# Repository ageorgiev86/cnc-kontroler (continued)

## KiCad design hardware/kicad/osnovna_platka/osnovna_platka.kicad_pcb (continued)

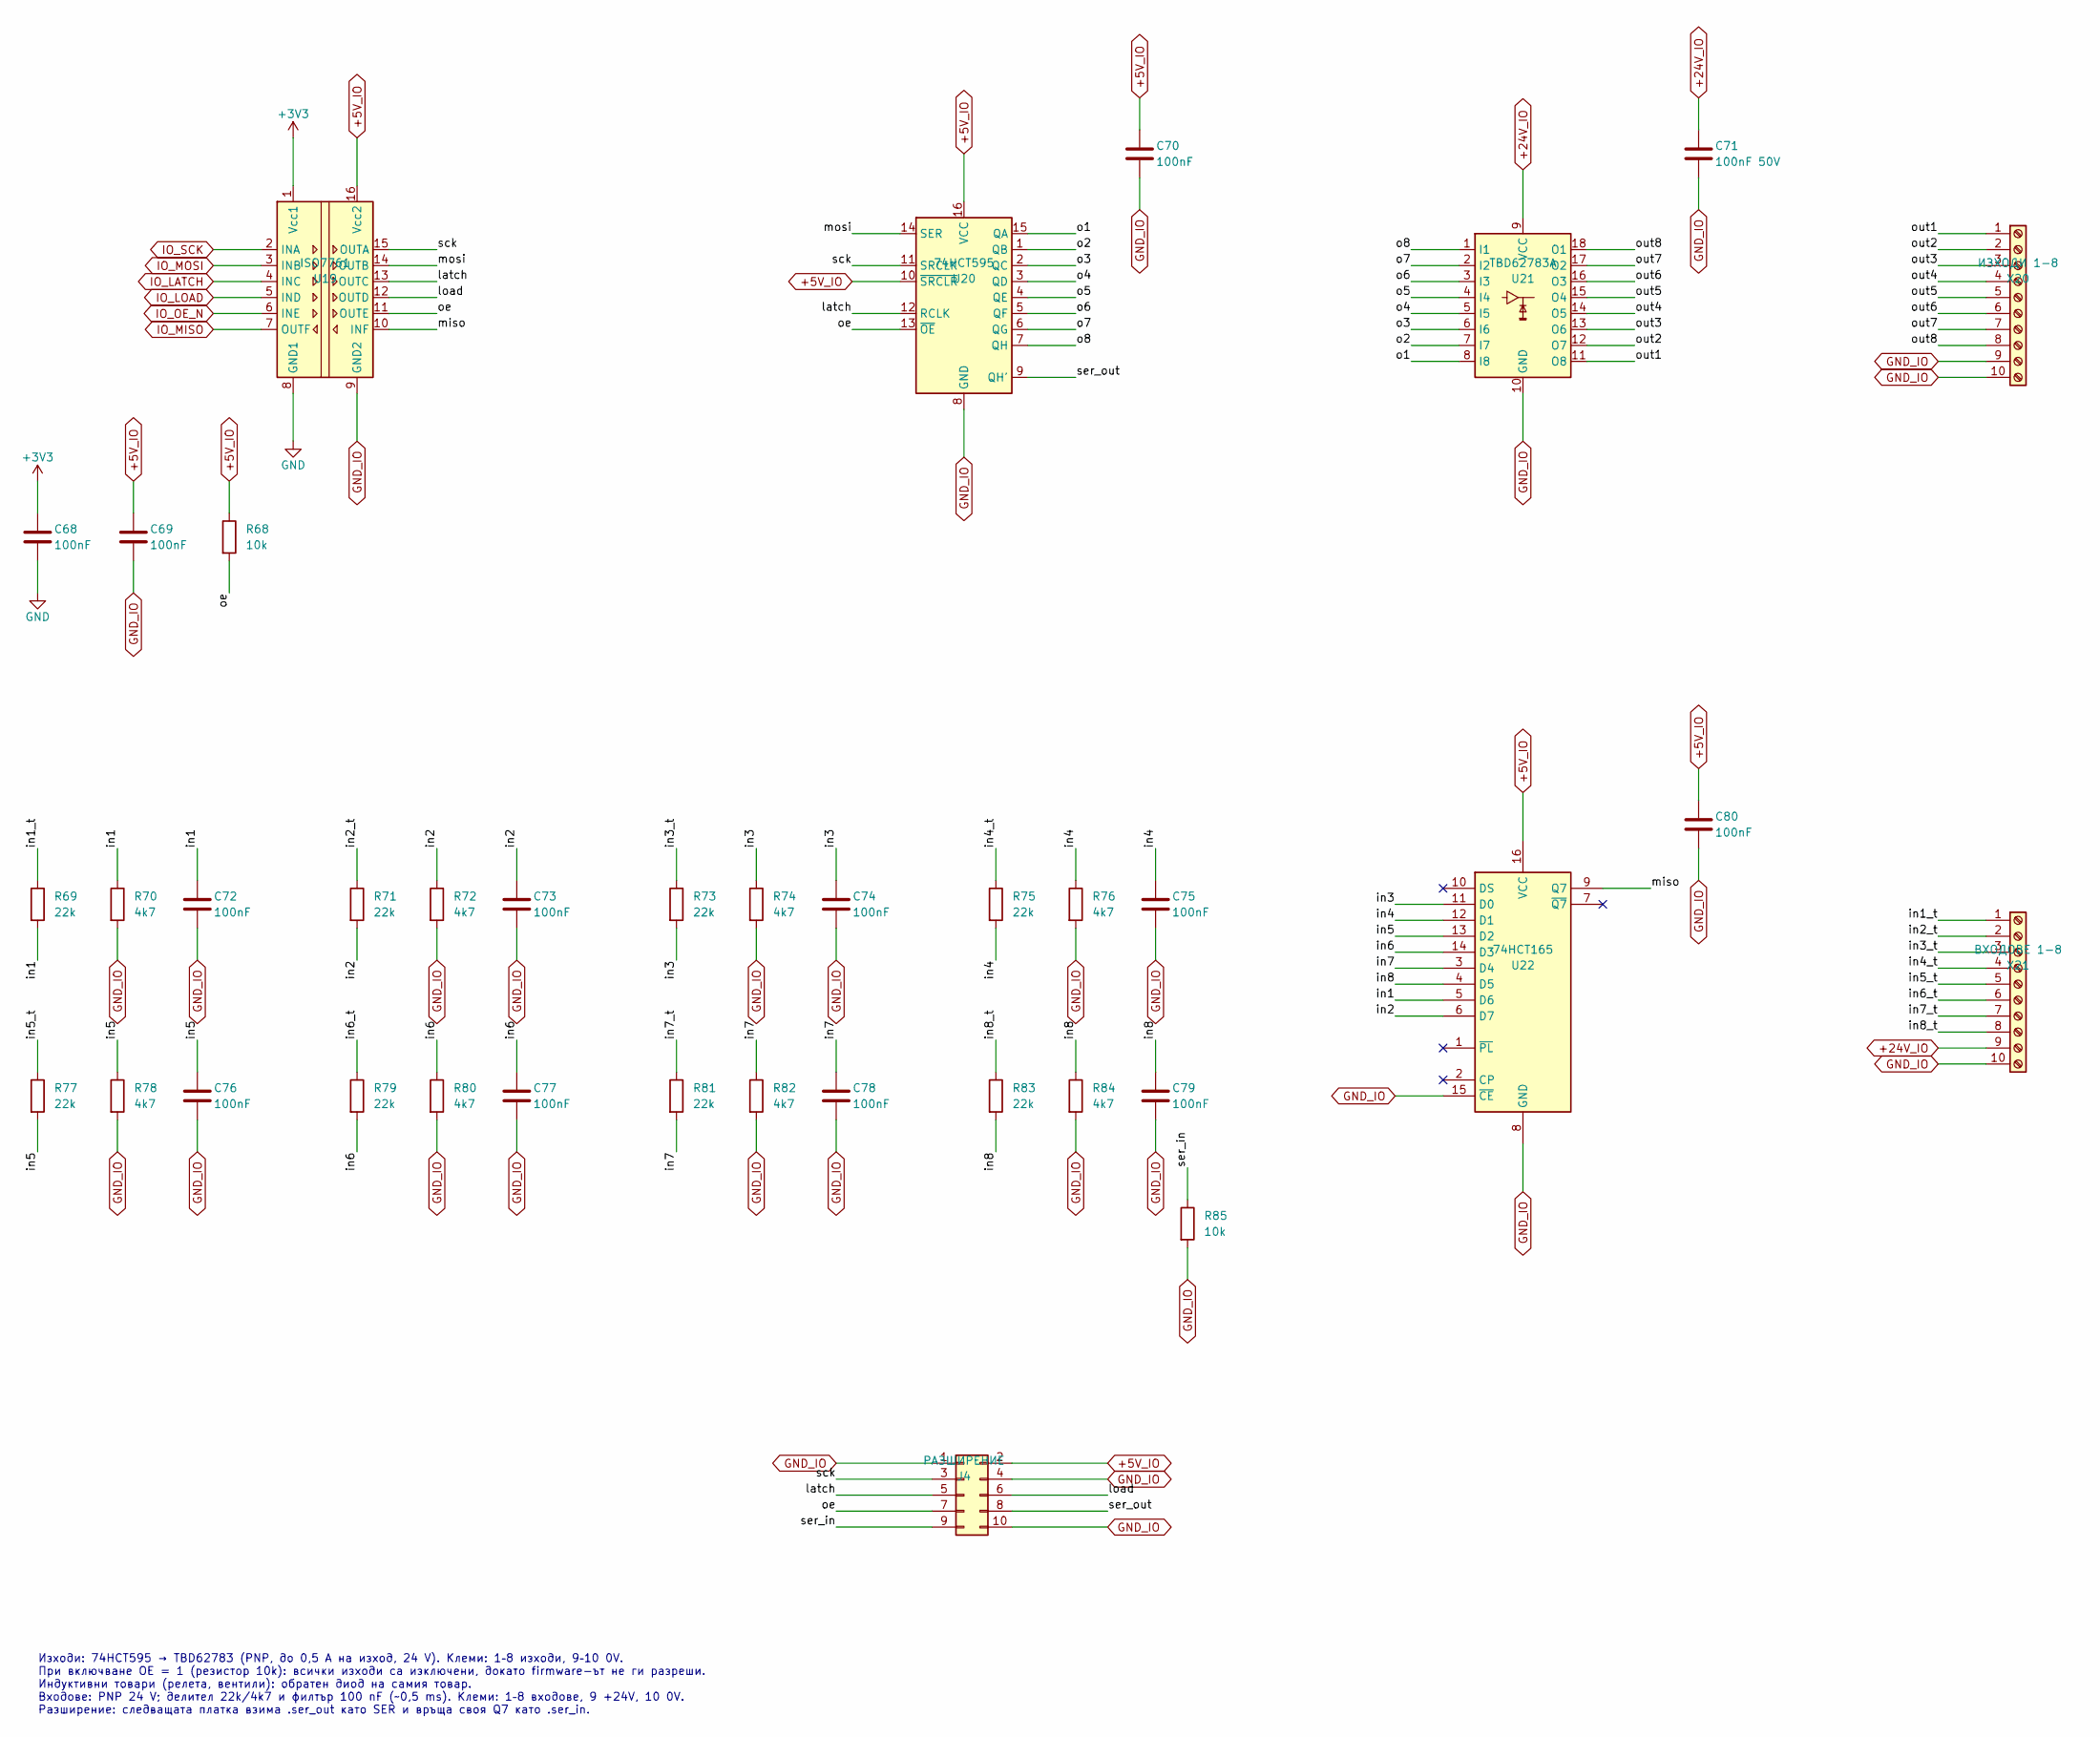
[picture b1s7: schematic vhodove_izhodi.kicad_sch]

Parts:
C68, C69, C70, C72, C73, C74, C75, C76, C77, C78, C79, C80: 100nF; C_0805_2012Metric
C71: 100nF 50V; C_0805_2012Metric
J4: РАЗШИРЕНИЕ; IDC-Header_2x05_P2.54mm_Vertical
R68, R85: 10k; R_0805_2012Metric
R69, R71, R73, R75, R77, R79, R81, R83: 22k; R_1206_3216Metric
R70, R72, R74, R76, R78, R80, R82, R84: 4k7; R_0805_2012Metric
U19: ISO7761; SOIC-16W_7.5x10.3mm_P1.27mm
U20: 74HCT595; SOIC-16_3.9x9.9mm_P1.27mm
U21: TBD62783A; SOIC-18W_7.5x11.6mm_P1.27mm
U22: 74HCT165; SOIC-16_3.9x9.9mm_P1.27mm
X20: ИЗХОДИ 1-8; PhoenixContact_MSTBA_2,5_10-G-5,08_1x10_P5.08mm_Horizontal
X21: ВХОДОВЕ 1-8; PhoenixContact_MSTBA_2,5_10-G-5,08_1x10_P5.08mm_Horizontal

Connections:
+3V3: C68.1, U19.1 (Vcc1); also elsewhere on the board
+5V_IO: C69.1, C70.1, C80.1, J4.2, R68.1, U19.16 (Vcc2), U20.10 (~SRCLR), U20.16 (VCC), U22.16 (VCC); also elsewhere on the board
+24V_IO: C71.1, U21.9 (VCC), X21.9; also elsewhere on the board
/Входове и изходи 8 + 8/in1: C72.1, R69.2, R70.1, U22.5 (D6)
/Входове и изходи 8 + 8/in1_t: R69.1, X21.1
/Входове и изходи 8 + 8/in2: C73.1, R71.2, R72.1, U22.6 (D7)
/Входове и изходи 8 + 8/in2_t: R71.1, X21.2
/Входове и изходи 8 + 8/in3: C74.1, R73.2, R74.1, U22.11 (D0)
/Входове и изходи 8 + 8/in3_t: R73.1, X21.3
/Входове и изходи 8 + 8/in4: C75.1, R75.2, R76.1, U22.12 (D1)
/Входове и изходи 8 + 8/in4_t: R75.1, X21.4
/Входове и изходи 8 + 8/in5: C76.1, R77.2, R78.1, U22.13 (D2)
/Входове и изходи 8 + 8/in5_t: R77.1, X21.5
/Входове и изходи 8 + 8/in6: C77.1, R79.2, R80.1, U22.14 (D3)
/Входове и изходи 8 + 8/in6_t: R79.1, X21.6
/Входове и изходи 8 + 8/in7: C78.1, R81.2, R82.1, U22.3 (D4)
/Входове и изходи 8 + 8/in7_t: R81.1, X21.7
/Входове и изходи 8 + 8/in8: C79.1, R83.2, R84.1, U22.4 (D5)
/Входове и изходи 8 + 8/in8_t: R83.1, X21.8
/Входове и изходи 8 + 8/latch: J4.5, U19.13 (OUTC), U20.12 (RCLK)
/Входове и изходи 8 + 8/load: J4.6, U19.12 (OUTD)
/Входове и изходи 8 + 8/miso: U19.10 (INF), U22.9 (Q7)
/Входове и изходи 8 + 8/mosi: U19.14 (OUTB), U20.14 (SER)
/Входове и изходи 8 + 8/o1: U20.15 (QA), U21.8 (I8)
/Входове и изходи 8 + 8/o2: U20.1 (QB), U21.7 (I7)
/Входове и изходи 8 + 8/o3: U20.2 (QC), U21.6 (I6)
/Входове и изходи 8 + 8/o4: U20.3 (QD), U21.5 (I5)
/Входове и изходи 8 + 8/o5: U20.4 (QE), U21.4 (I4)
/Входове и изходи 8 + 8/o6: U20.5 (QF), U21.3 (I3)
/Входове и изходи 8 + 8/o7: U20.6 (QG), U21.2 (I2)
/Входове и изходи 8 + 8/o8: U20.7 (QH), U21.1 (I1)
/Входове и изходи 8 + 8/oe: J4.7, R68.2, U19.11 (OUTE), U20.13 (~OE)
/Входове и изходи 8 + 8/out1: U21.11 (O8), X20.1
/Входове и изходи 8 + 8/out2: U21.12 (O7), X20.2
/Входове и изходи 8 + 8/out3: U21.13 (O6), X20.3
/Входове и изходи 8 + 8/out4: U21.14 (O5), X20.4
/Входове и изходи 8 + 8/out5: U21.15 (O4), X20.5
/Входове и изходи 8 + 8/out6: U21.16 (O3), X20.6
/Входове и изходи 8 + 8/out7: U21.17 (O2), X20.7
/Входове и изходи 8 + 8/out8: U21.18 (O1), X20.8
/Входове и изходи 8 + 8/sck: J4.3, U19.15 (OUTA), U20.11 (SRCLK)
/Входове и изходи 8 + 8/ser_in: J4.9, R85.1
/Входове и изходи 8 + 8/ser_out: J4.8, U20.9 (QH')
GND: C68.2, U19.8 (GND1); also elsewhere on the board
GND_IO: C69.2, C70.2, C71.2, C72.2, C73.2, C74.2, C75.2, C76.2, C77.2, C78.2, C79.2, C80.2, J4.1, J4.4, J4.10, R70.2, R72.2, R74.2, R76.2, R78.2, R80.2, R82.2, R84.2, R85.2, U19.9 (GND2), U20.8 (GND), U21.10 (GND), U22.8 (GND), U22.15 (~CE), X20.9, X20.10, X21.10; also elsewhere on the board
IO_LATCH: U19.4 (INC); also elsewhere on the board
IO_LOAD: U19.5 (IND); also elsewhere on the board
IO_MISO: U19.7 (OUTF); also elsewhere on the board
IO_MOSI: U19.3 (INB); also elsewhere on the board
IO_OE_N: U19.6 (INE); also elsewhere on the board
IO_SCK: U19.2 (INA); also elsewhere on the board

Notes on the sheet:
Изходи: 74HCT595 → TBD62783 (PNP, до 0,5 A на изход, 24 V). Клеми: 1–8 изходи, 9–10 0V. При включване OE = 1 (резистор 10k): всички изходи са изключени, докато firmware-ът не ги разреши. Индуктивни товари (релета, вентили): обратен диод на самия товар. Входове: PNP 24 V; делител 22k/4k7 и филтър 10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

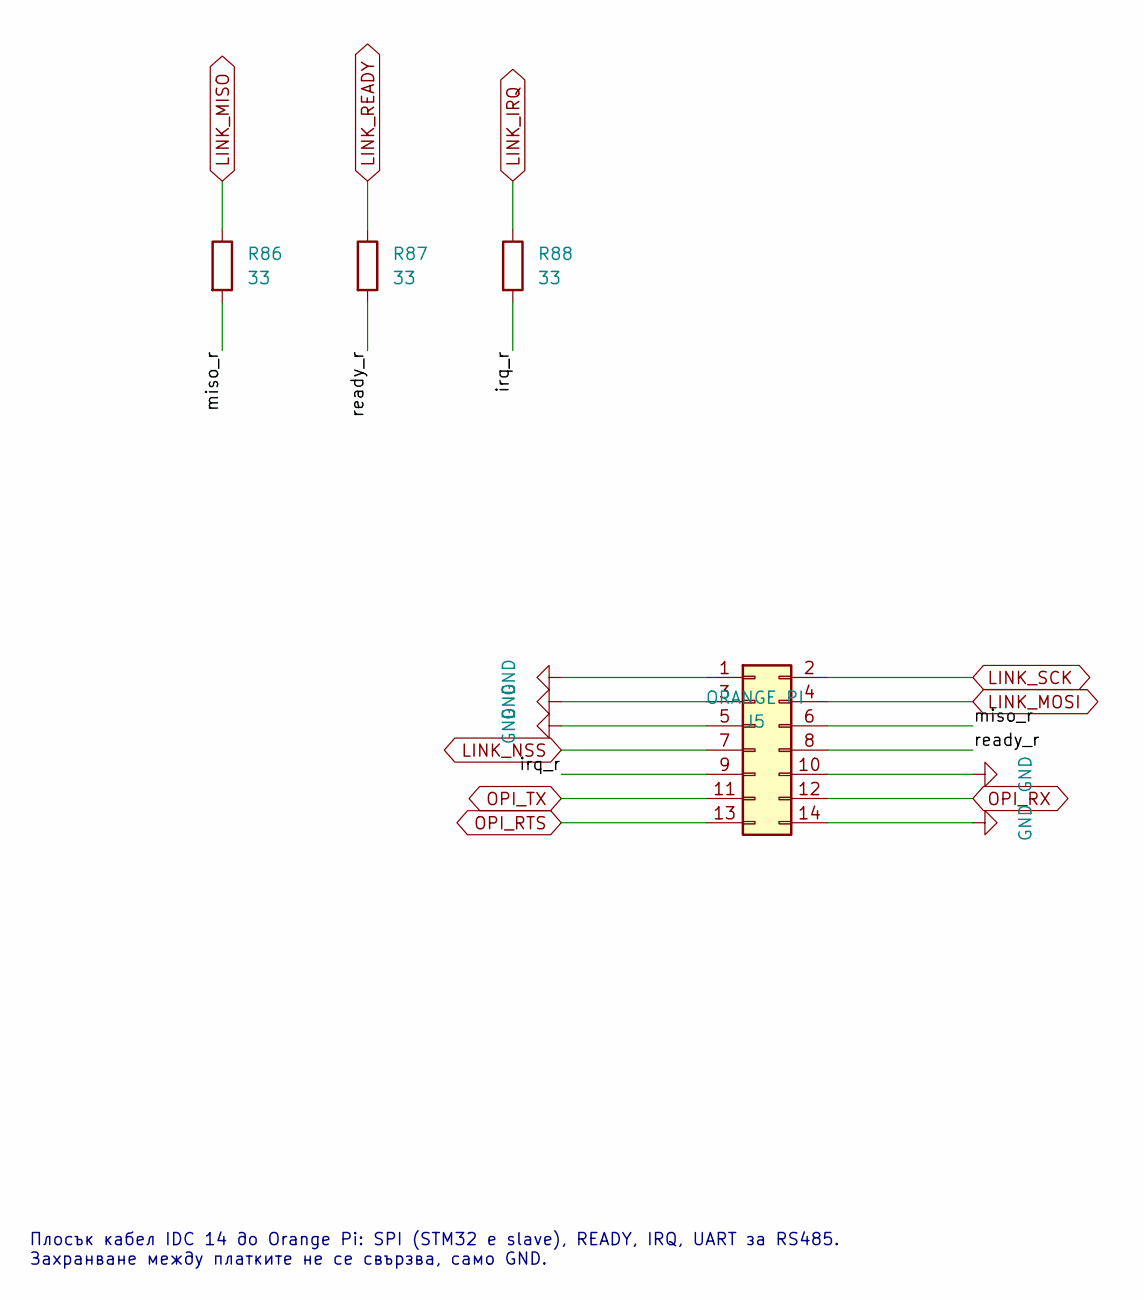
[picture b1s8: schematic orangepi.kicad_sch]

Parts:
J5: ORANGE PI; IDC-Header_2x07_P2.54mm_Vertical
R86, R87, R88: 33; R_0805_2012Metric

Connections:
/Orange Pi/irq_r: J5.9, R88.2
/Orange Pi/miso_r: J5.6, R86.2
/Orange Pi/ready_r: J5.8, R87.2
GND: J5.1, J5.3, J5.5, J5.10, J5.14; also elsewhere on the board
LINK_IRQ: R88.1; also elsewhere on the board
LINK_MISO: R86.1; also elsewhere on the board
LINK_MOSI: J5.4; also elsewhere on the board
LINK_NSS: J5.7; also elsewhere on the board
LINK_READY: R87.1; also elsewhere on the board
LINK_SCK: J5.2; also elsewhere on the board
OPI_RTS: J5.13; also elsewhere on the board
OPI_RX: J5.12; also elsewhere on the board
OPI_TX: J5.11; also elsewhere on the board

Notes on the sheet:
Плосък кабел IDC 14 до Orange Pi: SPI (STM32 е slave), READY, IRQ, UART за RS485. Захранване между платките не се свързва, само GND.

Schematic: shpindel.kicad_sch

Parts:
C81: 1uF; C_0805_2012Metric
C82: 100nF 50V; C_0805_2012Metric
C83: 100nF; C_0805_2012Metric
JP1: ТЕРМИНАТОР; PinHeader_1x02_P2.54mm_Vertical
R89, R91: 10k; R_0805_2012Metric
R90: 20k; R_0805_2012Metric
R92: 100; R_0805_2012Metric
R93, R94: 470; R_0805_2012Metric
R95, R96: 680; R_0805_2012Metric
R97: 120; R_0805_2012Metric
U23: LM358; SOIC-8_3.9x4.9mm_P1.27mm
U24, U25: PC817; SMDIP-4_W7.62mm
U26: THVD1450; SOIC-8_3.9x4.9mm_P1.27mm
X22: ЧЕСТОТЕН РЕГУЛАТОР; PhoenixContact_MSTBA_2,5_5-G-5,08_1x05_P5.08mm_Horizontal
X23: RS485; PhoenixContact_MSTBA_2,5_3-G-5,08_1x03_P5.08mm_Horizontal

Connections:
+3V3: C83.1, R95.1, U26.8 (VCC); also elsewhere on the board
+24V: C82.1, U23.8 (V+); also elsewhere on the board
/Шпиндел/aout: R90.1, R92.1, U23.1
/Шпиндел/avi: R92.2, X22.1
/Шпиндел/fb: R90.2, R91.1, U23.2 (-)
/Шпиндел/fwd: U24.4, X22.3
/Шпиндел/fwd_a: R93.2, U24.1
/Шпиндел/pwm_f: C81.1, R89.2, U23.3 (+)
/Шпиндел/rev: U25.4, X22.4
/Шпиндел/rev_a: R94.2, U25.1
/Шпиндел/rs_a: R95.2, R97.1, U26.6 (A), X23.1
/Шпиндел/rs_b: JP1.2, R96.1, U26.7 (B), X23.2
/Шпиндел/term: JP1.1, R97.2
/Шпиндел/u2o: U23.6 (-), U23.7
/Шпиндел/vfd_com: U24.3, U25.3, X22.5
GND: C81.2, C82.2, C83.2, R91.2, R96.2, U23.4 (V-), U23.5 (+), U24.2, U25.2, U26.5 (GND), X22.2, X23.3; also elsewhere on the board
OPI_RTS: U26.2 (~RE), U26.3 (DE); also elsewhere on the board
OPI_RX: U26.1 (RO); also elsewhere on the board
OPI_TX: U26.4 (DI); also elsewhere on the board
SPINDLE_DIR: R94.1; also elsewhere on the board
SPINDLE_EN: R93.1; also elsewhere on the board
SPINDLE_PWM: R89.1; also elsewhere on the board

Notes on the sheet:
Регулатор: 1 AVI (0–10 V) 2 ACM 3 FWD 4 REV 5 COM. 0–10 V не е изолиран. RS485 (Modbus от Orange Pi): джъмперът включва 120 Ω само на края на линията.

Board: 2 copper layers, 286 parts (0 on the bottom side), 249 nets, no tracks yet.

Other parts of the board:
H1, H2, H3, H4: M3; MountingHole_3.2mm_M3

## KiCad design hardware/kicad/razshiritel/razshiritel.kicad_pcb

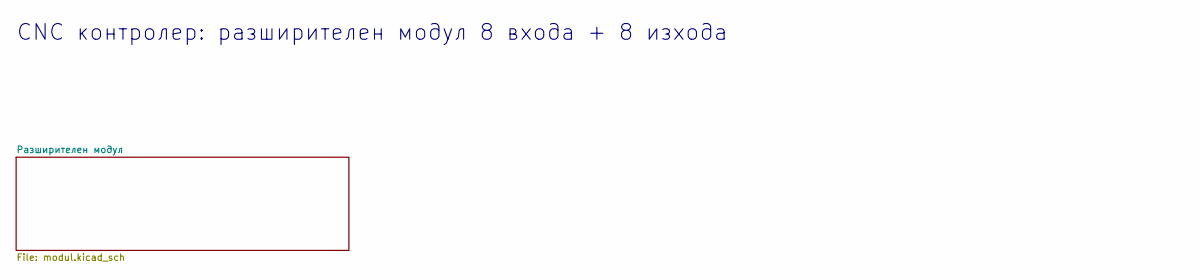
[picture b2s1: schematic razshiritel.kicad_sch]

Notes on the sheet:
CNC контролер: разширителен модул 8 входа + 8 изхода

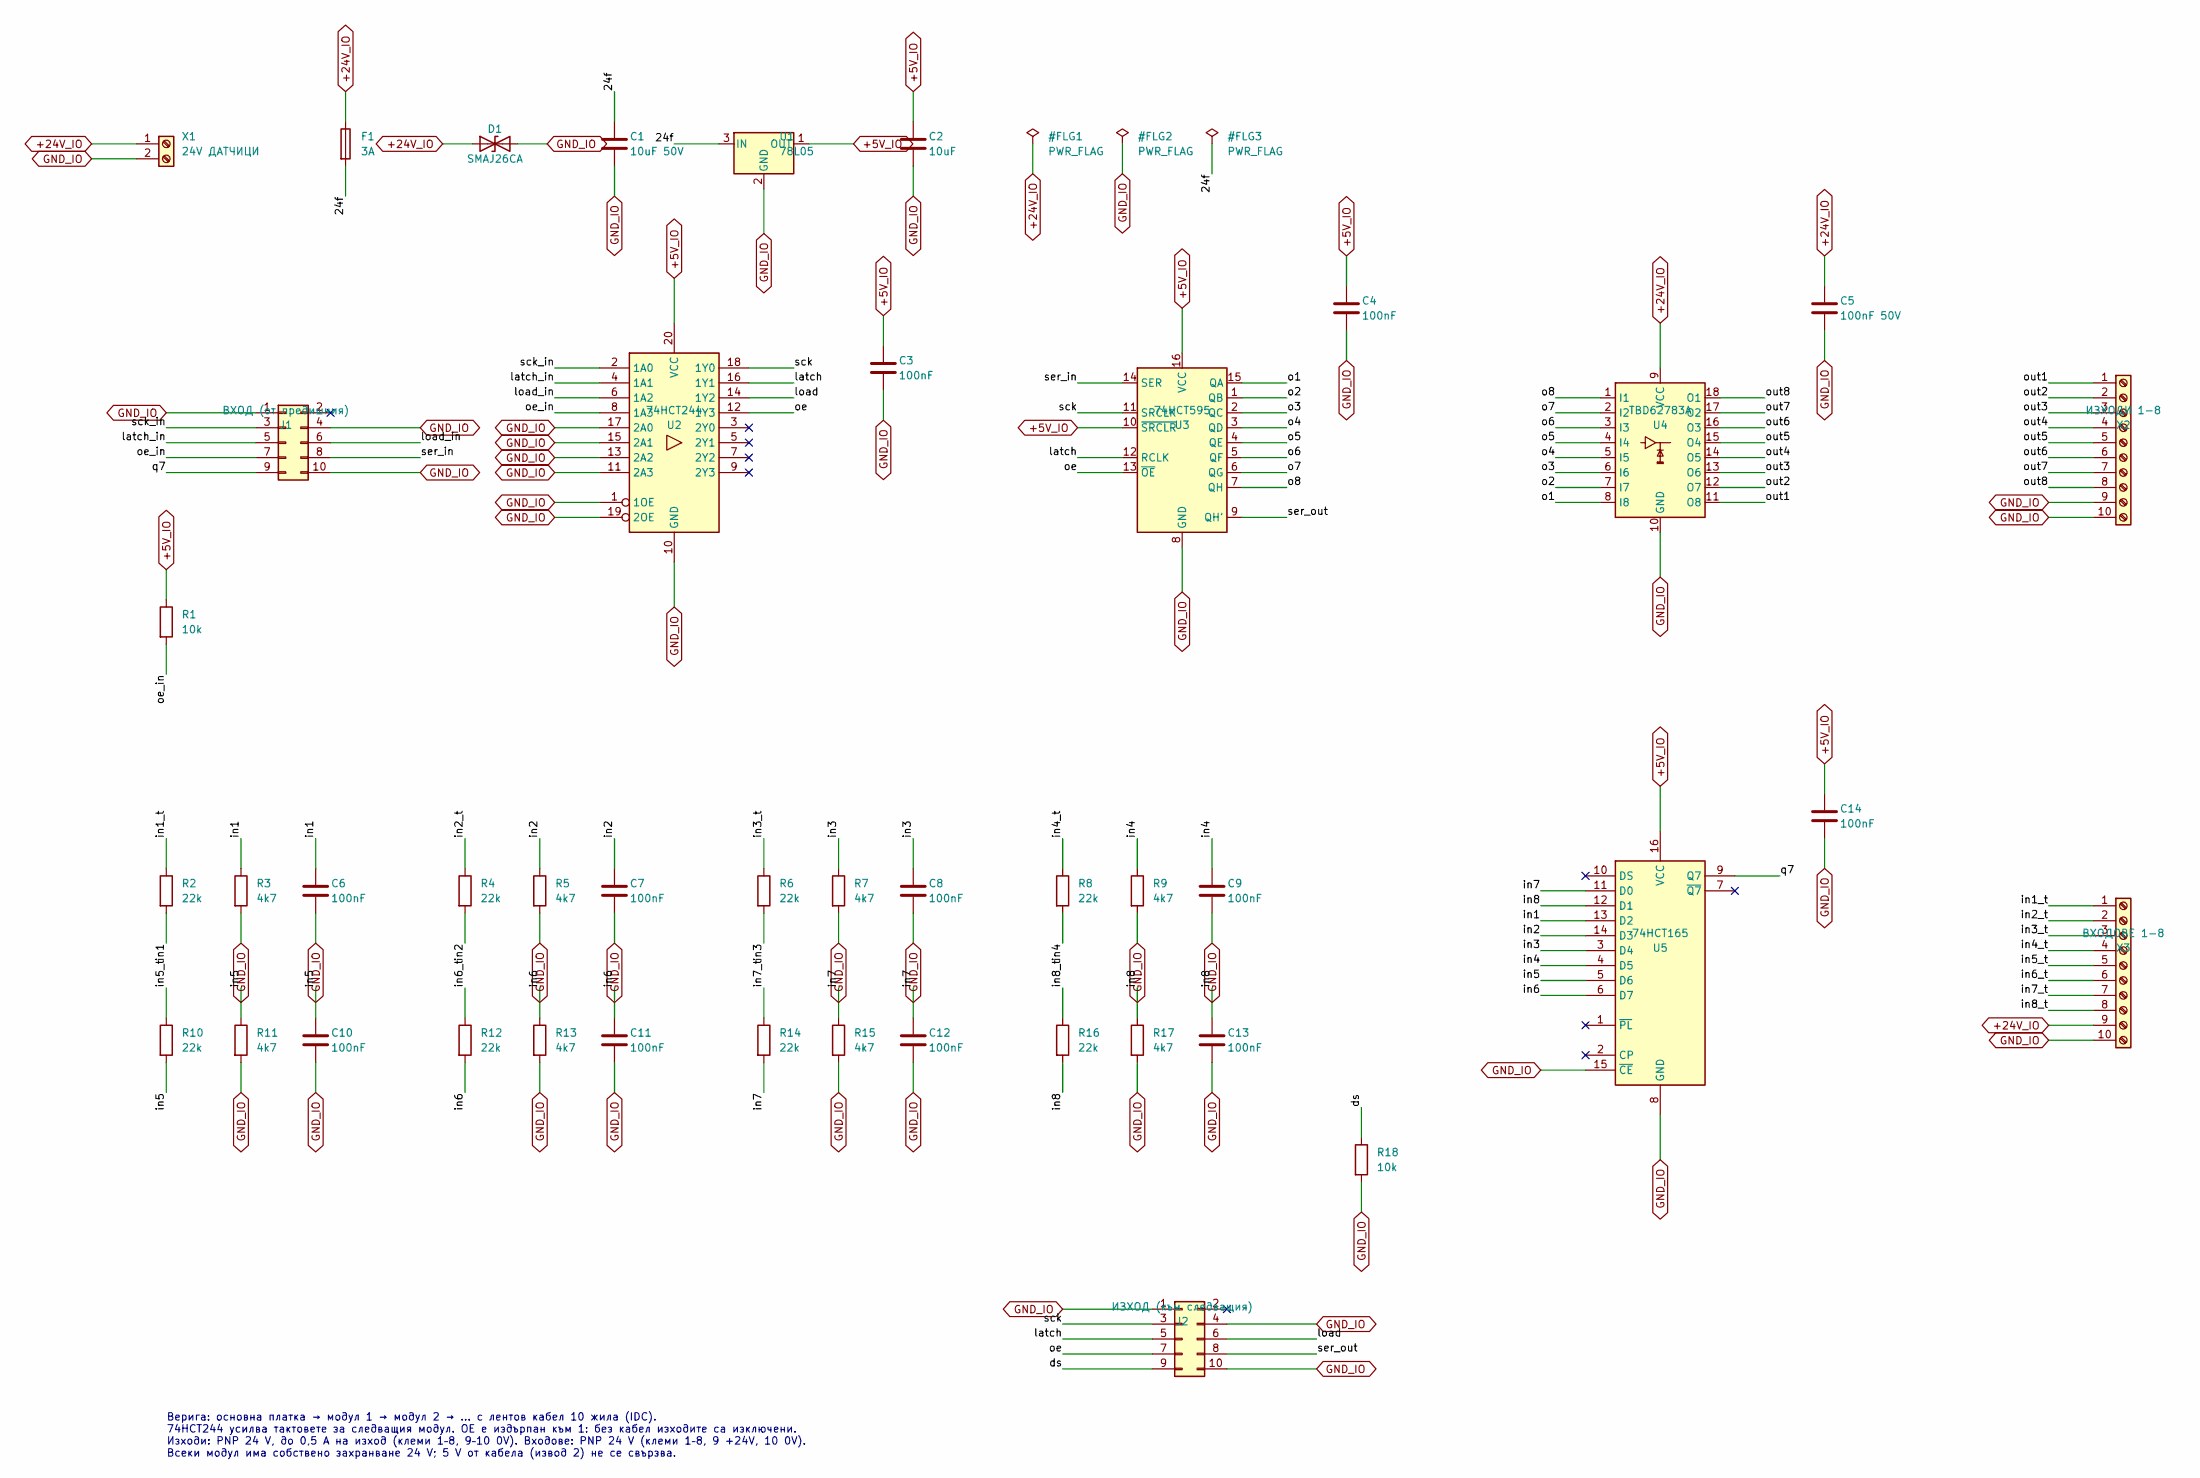
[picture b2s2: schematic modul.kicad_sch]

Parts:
C1: 10uF 50V; C_1210_3225Metric
C2: 10uF; C_1206_3216Metric
C3, C4, C6, C7, C8, C9, C10, C11, C12, C13, C14: 100nF; C_0805_2012Metric
C5: 100nF 50V; C_0805_2012Metric
D1: SMAJ26CA; D_SMA
F1: 3A; Fuse_1812_4532Metric
J1: ВХОД (от предишния); IDC-Header_2x05_P2.54mm_Vertical
J2: ИЗХОД (към следващия); IDC-Header_2x05_P2.54mm_Vertical
R1, R18: 10k; R_0805_2012Metric
R2, R4, R6, R8, R10, R12, R14, R16: 22k; R_1206_3216Metric
R3, R5, R7, R9, R11, R13, R15, R17: 4k7; R_0805_2012Metric
U1: 78L05; SOT-89-3
U2: 74HCT244; SOIC-20W_7.5x12.8mm_P1.27mm
U3: 74HCT595; SOIC-16_3.9x9.9mm_P1.27mm
U4: TBD62783A; SOIC-18W_7.5x11.6mm_P1.27mm
U5: 74HCT165; SOIC-16_3.9x9.9mm_P1.27mm
X1: 24V ДАТЧИЦИ; PhoenixContact_MSTBA_2,5_2-G-5,08_1x02_P5.08mm_Horizontal
X2: ИЗХОДИ 1-8; PhoenixContact_MSTBA_2,5_10-G-5,08_1x10_P5.08mm_Horizontal
X3: ВХОДОВЕ 1-8; PhoenixContact_MSTBA_2,5_10-G-5,08_1x10_P5.08mm_Horizontal

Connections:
+5V_IO: C2.1, C3.1, C4.1, C14.1, R1.1, U1.1 (OUT), U2.20 (VCC), U3.10 (~SRCLR), U3.16 (VCC), U5.16 (VCC)
+24V_IO: C5.1, D1.1 (A1), F1.1, U4.9 (VCC), X1.1, X3.9
/Разширителен модул/24f: C1.1, F1.2, U1.3 (IN)
/Разширителен модул/ds: J2.9, R18.1
/Разширителен модул/in1: C6.1, R2.2, R3.1, U5.13 (D2)
/Разширителен модул/in1_t: R2.1, X3.1
/Разширителен модул/in2: C7.1, R4.2, R5.1, U5.14 (D3)
/Разширителен модул/in2_t: R4.1, X3.2
/Разширителен модул/in3: C8.1, R6.2, R7.1, U5.3 (D4)
/Разширителен модул/in3_t: R6.1, X3.3
/Разширителен модул/in4: C9.1, R8.2, R9.1, U5.4 (D5)
/Разширителен модул/in4_t: R8.1, X3.4
/Разширителен модул/in5: C10.1, R10.2, R11.1, U5.5 (D6)
/Разширителен модул/in5_t: R10.1, X3.5
/Разширителен модул/in6: C11.1, R12.2, R13.1, U5.6 (D7)
/Разширителен модул/in6_t: R12.1, X3.6
/Разширителен модул/in7: C12.1, R14.2, R15.1, U5.11 (D0)
/Разширителен модул/in7_t: R14.1, X3.7
/Разширителен модул/in8: C13.1, R16.2, R17.1, U5.12 (D1)
/Разширителен модул/in8_t: R16.1, X3.8
/Разширителен модул/latch: J2.5, U2.16 (1Y1), U3.12 (RCLK)
/Разширителен модул/latch_in: J1.5, U2.4 (1A1)
/Разширителен модул/load: J2.6, U2.14 (1Y2)
/Разширителен модул/load_in: J1.6, U2.6 (1A2)
/Разширителен модул/o1: U3.15 (QA), U4.8 (I8)
/Разширителен модул/o2: U3.1 (QB), U4.7 (I7)
/Разширителен модул/o3: U3.2 (QC), U4.6 (I6)
/Разширителен модул/o4: U3.3 (QD), U4.5 (I5)
/Разширителен модул/o5: U3.4 (QE), U4.4 (I4)
/Разширителен модул/o6: U3.5 (QF), U4.3 (I3)
/Разширителен модул/o7: U3.6 (QG), U4.2 (I2)
/Разширителен модул/o8: U3.7 (QH), U4.1 (I1)
/Разширителен модул/oe: J2.7, U2.12 (1Y3), U3.13 (~OE)
/Разширителен модул/oe_in: J1.7, R1.2, U2.8 (1A3)
/Разширителен модул/out1: U4.11 (O8), X2.1
/Разширителен модул/out2: U4.12 (O7), X2.2
/Разширителен модул/out3: U4.13 (O6), X2.3
/Разширителен модул/out4: U4.14 (O5), X2.4
/Разширителен модул/out5: U4.15 (O4), X2.5
/Разширителен модул/out6: U4.16 (O3), X2.6
/Разширителен модул/out7: U4.17 (O2), X2.7
/Разширителен модул/out8: U4.18 (O1), X2.8
/Разширителен модул/q7: J1.9, U5.9 (Q7)
/Разширителен модул/sck: J2.3, U2.18 (1Y0), U3.11 (SRCLK)
/Разширителен модул/sck_in: J1.3, U2.2 (1A0)
/Разширителен модул/ser_in: J1.8, U3.14 (SER)
/Разширителен модул/ser_out: J2.8, U3.9 (QH')
GND_IO: C1.2, C2.2, C3.2, C4.2, C5.2, C6.2, C7.2, C8.2, C9.2, C10.2, C11.2, C12.2, C13.2, C14.2, D1.2 (A2), J1.1, J1.4, J1.10, J2.1, J2.4, J2.10, R3.2, R5.2, R7.2, R9.2, R11.2, R13.2, R15.2, R17.2, R18.2, U1.2 (GND), U2.1 (1OE), U2.10 (GND), U2.11 (2A3), U2.13 (2A2), U2.15 (2A1), U2.17 (2A0), U2.19 (2OE), U3.8 (GND), U4.10 (GND), U5.8 (GND), U5.15 (~CE), X1.2, X2.9, X2.10, X3.10

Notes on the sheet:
Верига: основна платка → модул 1 → модул 2 → ... с лентов кабел 10 жила (IDC). 74HCT244 усилва тактовете за следващия модул. OE е издърпан към 1: без кабел изходите са изключени. Изходи: PNP 24 V, до 0,5 A на изход (клеми 1–8, 9–10 0V). Входове: PNP 24 V (клеми 1–8, 9 +24V, 10 0V). Всеки модул има 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

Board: 2 copper layers, 48 parts (0 on the bottom side), 48 nets, no tracks yet.

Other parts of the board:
H1, H2, H3, H4: M3; MountingHole_3.2mm_M3

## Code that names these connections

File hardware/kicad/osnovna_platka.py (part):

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# ---------------------------------------------------------------------------
MCU = {
    # енкодери (таймер в encoder mode: A = CH1, B = CH2)
    'PA0': 'ENC1_A', 'PA1': 'ENC1_B',          # TIM5
    'PA15': 'ENC2_A', 'PB3': 'ENC2_B',         # TIM2
    'PF0': 'ENC3_A', 'PF1': 'ENC3_B',          # TIM23
    'PB4': 'ENC4_A', 'PB5': 'ENC4_B',          # TIM3
    'PB6': 'ENC5_A', 'PB7': 'ENC5_B',          # TIM4
    'PA8': 'ENC6_A', 'PA9': 'ENC6_B',          # TIM1
    'PF11': 'ENC_SP_A', 'PF12': 'ENC_SP_B',    # TIM24
    # MPG пулт: отделен модул по RS-485 (UART4, AF8), посоката от PD3
    'PD0': 'MPG_RX', 'PD1': 'MPG_TX', 'PD3': 'MPG_DE',
    # стъпки и посока, канал 1–6 (един порт: DMA → GPIOD BSRR)
    'PD4': 'STEP1', 'PD5': 'DIR1', 'PD6': 'STEP2', 'PD7': 'DIR2', 'PD8': 'STEP3', 'PD9': 'DIR3',
    'PD10': 'STEP4', 'PD11': 'DIR4', 'PD12': 'STEP5', 'PD13': 'DIR5', 'PD14': 'STEP6', 'PD15': 'DIR6',
    'PB11': 'DRV_EN', 'PE3': 'DRV_FAULT', 'PE9': 'DRV_OE_N',
    # крайни изключватели и HOME, канал 1–6 (активни при 0 след оптрона)
    'PG8': 'LIM1', 'PG9': 'LIM2', 'PG10': 'LIM3', 'PG11': 'LIM4', 'PG12': 'LIM5', 'PG13': 'LIM6',
    'PG14': 'HOME1', 'PG15': 'HOME2', 'PF6': 'HOME3', 'PF7': 'HOME4', 'PF8': 'HOME5', 'PF9': 'HOME6',
    # връзка с Orange Pi (SPI4 slave)
    'PE11': 'LINK_NSS', 'PE12': 'LINK_SCK', 'PE13': 'LINK_MISO', 'PE14': 'LINK_MOSI',
    'PE15': 'LINK_READY', 'PE10': 'LINK_IRQ',
    # входове и изходи (SPI2 master към 74HCT595 / 74HCT165 през изолатора)
    'PB13': 'IO_SCK', 'PB14': 'IO_MISO', 'PB15': 'IO_MOSI', 'PB12': 'IO_LATCH', 'PE7': 'IO_LOAD',
    'PE8': 'IO_OE_N',
    # бързи входове
    'PA7': 'PROBE', 'PB1': 'TOOLSETTER', 'PC13': 'ESTOP_SENSE',
    # шпиндел
    'PB9': 'SPINDLE_PWM', 'PC4': 'SPINDLE_DIR', 'PC5': 'SPINDLE_EN',
    # процесорна част
    'PA11': '.usb_dm', 'PA12': '.usb_dp', 'PA13': 'SWDIO', 'PA14': 'SWCLK',
    'PH0': '.hse_in', 'PH1': '.hse_out', 'PC14': '.lse_in', 'PC15': '.lse_out',
    'PG7': '.led',
    'NRST': 'NRST', 'BOOT0': '.boot0', 'PDR_ON': '+3V3', 'VBAT': '.vbat',
    'VDD': '+3V3', 'VDD33USB': '+3V3', 'VDDA': '.vdda', 'VREF+': '.vdda', 'VSS': 'GND', 'VSSA': 'GND',
    71: '.vcap1', 106: '.vcap2',     # VCAP: всеки със свой кондензатор (не се свързват заедно)
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    flag(sh, 271.78, 330.2, '.vdda')

    place(sh, 'Device:Crystal_GND24', 'Y', '25MHz', 360.68, 50.8,
          {1: '.hse_in', 3: '.hse_out', 2: 'GND', 4: 'GND'}, footprint='Crystal:Crystal_SMD_3225-4Pin_3.2x2.5mm',
          role='mcu.hse')
    C(sh, 381, 50.8, '22pF', '.hse_in', 'GND', 'mcu.chse1')
    C(sh, 393.7, 50.8, '22pF', '.hse_out', 'GND', 'mcu.chse2')
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    R(sh, x, y, '4k7', '.estop_in', '.estop_a', 'in.estop.r', FP_R1206)
    place(sh, 'Device:D', 'D', '1N4148W', x + 15.24, y + 10.16, {'A': 'GND_IO', 'K': '.estop_a'}, footprint=FP_SOD,
          role='in.estop.d')
    place(sh, 'Isolator:PC817', 'U', 'PC817', x + 40.64, y, {1: '.estop_a', 2: 'GND_IO', 3: 'GND', 4: 'ESTOP_SENSE'},
          footprint=FP_PC817, stub=7.62, role='in.estop.u')
    R(sh, x + 66.04, y, '10k', '+3V3', 'ESTOP_SENSE', 'in.estop.pu')
    C(sh, x + 78.74, y, '10nF', 'ESTOP_SENSE', 'GND', 'in.estop.c')
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# ---------------------------------------------------------------------------
def sheet_links(project):
    sh = Sheet('orangepi', 'Orange Pi', project)
    for i, (net, loc) in enumerate((('LINK_MISO', '.miso_r'), ('LINK_READY', '.ready_r'), ('LINK_IRQ', '.irq_r'))):
        R(sh, 45.72 + i * 15.24, 50.8, '33', net, loc, f'opi.r{i + 1}')
    place(sh, 'Connector_Generic:Conn_02x07_Odd_Even', 'J', 'ORANGE PI', 101.6, 101.6, {
        1: 'GND', 2: 'LINK_SCK', 3: 'GND', 4: 'LINK_MOSI', 5: 'GND', 6: '.miso_r', 7: 'LINK_NSS',
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# ---------------------------------------------------------------------------
def sheet_spindle(project):
    sh = Sheet('shpindel', 'Шпиндел', project)
    R(sh, 30.48, 50.8, '10k', 'SPINDLE_PWM', '.pwm_f', 'vfd.rf')
    C(sh, 45.72, 63.5, '1uF', '.pwm_f', 'GND', 'vfd.cf')
    ref = place(sh, 'Amplifier_Operational:LM358', 'U', 'LM358', 81.28, 55.88,
                {'+': '.pwm_f', '-': '.fb', 1: '.aout'}, footprint=FP_SOIC8, unit=1, role='vfd.op')
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    R(sh, 111.76, 50.8, '20k', '.aout', '.fb', 'vfd.rfb')
    R(sh, 111.76, 71.12, '10k', '.fb', 'GND', 'vfd.rg')
    R(sh, 129.54, 50.8, '100', '.aout', '.avi', 'vfd.rout')
    for i, (sig, out, nm) in enumerate((('SPINDLE_EN', '.fwd', 'fwd'), ('SPINDLE_DIR', '.rev', 'rev'))):
        x = 182.88 + i * 60.96
        R(sh, x, 50.8, '470', sig, f'{out}_a', f'vfd.{nm}.r')
        place(sh, 'Isolator:PC817', 'U', 'PC817', x + 27.94, 50.8,
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
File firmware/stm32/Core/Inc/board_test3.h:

/*
 * Тестова 3-осна машина: модул FK723M1-ZGT6 + собствена тестова платка.
 * Copyright (c) 2026 ageorgiev86. Всички права запазени.
 *
 * Компилира се с конфигурацията Test3 (cmake --preset Test3): CNC_BOARD=test3 → BOARD_TEST3.
 * Таблицата и схемите на входовете и изходите: docs/test-masina-3osi.md.
 *
 * Сигнали:
 *   - датчиците и бутоните са на 5 V, но само свалят пина към GND (механичен ключ или
 *     NPN с отворен колектор); пинът е с вътрешно издърпване към 3,3 V → 0 = активен;
 *   - драйверите 2HSS57 през 74ACT245 на 5 V, общ анод → импулсът е 0;
 *   - изходите (въздух, шпиндел) през ULN2803 към релетата и вентилите;
 *   - датчик за налягане 0–5 V през делител 12 kΩ / 20 kΩ към PC0.
 * Избягват се пиновете на флаш паметта (PF6–PF10, PG6) и на microSD (PC8–PC12, PD2).
 */
#ifndef BOARD_TEST3_H
#define BOARD_TEST3_H

#define BOARD_NAME            "тестова 3-осна машина (FK723M1)"

/* Светодиод на модула: PG7, свети при 0 */
#define BOARD_LED_PORT        GPIOG
#define BOARD_LED_PIN         GPIO_PIN_7
#define BOARD_LED_CLK_ENABLE() __HAL_RCC_GPIOG_CLK_ENABLE()
#define BOARD_LED_ACTIVE_LOW  1

#define BOARD_SUPPLY          PWR_LDO_SUPPLY

/* Стъпки и посока: X PD4/PD5, Y PD6/PD7, Z PD8/PD9 (PD10–PD15 за A, B, C остават свободни) */
#define BOARD_STEP_PORT         GPIOD
#define BOARD_STEP_CLK_ENABLE() __HAL_RCC_GPIOD_CLK_ENABLE()
#define BOARD_STEP_PINS  { GPIO_PIN_4, GPIO_PIN_6, GPIO_PIN_8, GPIO_PIN_10, GPIO_PIN_12, GPIO_PIN_14 }
#define BOARD_DIR_PINS   { GPIO_PIN_5, GPIO_PIN_7, GPIO_PIN_9, GPIO_PIN_11, GPIO_PIN_13, GPIO_PIN_15 }
#define BOARD_AXES_MAX          6
#define BOARD_STEP_ACTIVE_LOW   1                    /* 74ACT245 + общ анод: импулсът е 0 */

#define BOARD_DRV_EN            GPIOB, GPIO_PIN_11   /* ENA (още не се управлява) */
#define BOARD_DRV_FAULT         GPIOE, GPIO_PIN_3    /* ALM на трите драйвера успоредно, 0 = аларма */
#define BOARD_DRV_OE_PORT       GPIOE                /* ~OE на 74ACT245 (10 kΩ към 5 V), 0 = разрешени */
#define BOARD_DRV_OE_PIN        GPIO_PIN_9
#define BOARD_DRV_OE_N          BOARD_DRV_OE_PORT, BOARD_DRV_OE_PIN
#define BOARD_DRV_OE_CLK_ENABLE() __HAL_RCC_GPIOE_CLK_ENABLE()

/* Входове, 0 = активен */
#define BOARD_LIM1              GPIOG, GPIO_PIN_8    /* X */
#define BOARD_LIM2              GPIOG, GPIO_PIN_9    /* Y */
#define BOARD_LIM3              GPIOG, GPIO_PIN_10   /* Z */
#define BOARD_HOME1             GPIOG, GPIO_PIN_14   /* X */
#define BOARD_HOME2             GPIOG, GPIO_PIN_15   /* Y */
#define BOARD_HOME3             GPIOE, GPIO_PIN_10   /* Z (не PF6: флаш паметта) */
#define BOARD_PROBE             GPIOA, GPIO_PIN_7
#define BOARD_TOOLSETTER        GPIOB, GPIO_PIN_1
#define BOARD_ESTOP             GPIOC, GPIO_PIN_13   /* наблюдение; аварийният стоп е хардуерен */
#define BOARD_BTN_START         GPIOG, GPIO_PIN_0
#define BOARD_BTN_STOP          GPIOG, GPIO_PIN_1
#define BOARD_MPG_X             GPIOG, GPIO_PIN_2
#define BOARD_MPG_Y             GPIOG, GPIO_PIN_3
#define BOARD_MPG_Z             GPIOG, GPIO_PIN_4
#define BOARD_MPG_X1            GPIOF, GPIO_PIN_2
#define BOARD_MPG_X10           GPIOF, GPIO_PIN_3
#define BOARD_MPG_X100          GPIOF, GPIO_PIN_4

/* редът е битовете на STATUS.local_in (inputs.h); { NULL, 0 } = няма вход */
#define BOARD_INPUTS { \
  { BOARD_LIM1 }, { BOARD_LIM2 }, { BOARD_LIM3 }, { NULL, 0 }, { NULL, 0 }, { NULL, 0 }, \
  { BOARD_HOME1 }, { BOARD_HOME2 }, { BOARD_HOME3 }, { NULL, 0 }, { NULL, 0 }, { NULL, 0 }, \
  { BOARD_PROBE }, { BOARD_TOOLSETTER }, { BOARD_ESTOP }, { BOARD_DRV_FAULT }, \
  { BOARD_BTN_START }, { BOARD_BTN_STOP }, { BOARD_MPG_X }, { BOARD_MPG_Y }, { BOARD_MPG_Z }, \
  { BOARD_MPG_X1 }, { BOARD_MPG_X10 }, { BOARD_MPG_X100 } }
#define BOARD_IN_INVERT         0u                   /* битове, при които 1 на пина = активен (NC ключ) */
#define BOARD_LIM_MASK          0x07u                /* крайните изключватели, които спират машината */

/* MPG колело: TIM8 в encoder mode, A = PC6, B = PC7 (1 kΩ последователно) */
#define BOARD_MPG_TIM           TIM8
#define BOARD_MPG_TIM_CLK_ENABLE() __HAL_RCC_TIM8_CLK_ENABLE()
#define BOARD_MPG_AF            GPIO_AF3_TIM8
#define BOARD_MPG_A             GPIOC, GPIO_PIN_6
#define BOARD_MPG_B             GPIOC, GPIO_PIN_7

/* Изходи през ULN2803: бит 0 = OUT1 */
#define BOARD_OUTPUTS { { GPIOE, GPIO_PIN_0 } /* OUT1 въздух */, { GPIOE, GPIO_PIN_1 } /* OUT2 */, { GPIOE, GPIO_PIN_2 } /* OUT3 */ }

/* Шпиндел: релета FWD и REV (през ULN2803) */
#define BOARD_SPINDLE_DIR       GPIOC, GPIO_PIN_4    /* REV */
#define BOARD_SPINDLE_EN        GPIOC, GPIO_PIN_5    /* FWD */

/* Връзка с Linux: SPI4 slave, същите пинове като на основната платка (PE11–PE14, READY PE15);
 * IRQ (PE10 на основната платка) тук е HOME Z и не се ползва */
#define BOARD_LINK_SPI          SPI4
#define BOARD_LINK_AF           GPIO_AF5_SPI4
#define BOARD_LINK_NSS          GPIOE, GPIO_PIN_11
#define BOARD_LINK_SCK          GPIOE, GPIO_PIN_12
#define BOARD_LINK_MISO         GPIOE, GPIO_PIN_13
#define BOARD_LINK_MOSI         GPIOE, GPIO_PIN_14
#define BOARD_LINK_READY        GPIOE, GPIO_PIN_15   /* изход: готов за пакет */

/* Аналогов вход 1: датчик за налягане 0–5 V → делител 12 kΩ / 20 kΩ → PC0 (ADC1_INP10) */
#define BOARD_AIN1_PORT         GPIOC
#define BOARD_AIN1_PIN          GPIO_PIN_0
#define BOARD_AIN1_CHANNEL      ADC_CHANNEL_10
#define BOARD_AIN1_SCALE_X1000  1600u                /* (12 + 20) / 20: напрежение на датчика = на пина × 1,6 */

#endif /* BOARD_TEST3_H */
